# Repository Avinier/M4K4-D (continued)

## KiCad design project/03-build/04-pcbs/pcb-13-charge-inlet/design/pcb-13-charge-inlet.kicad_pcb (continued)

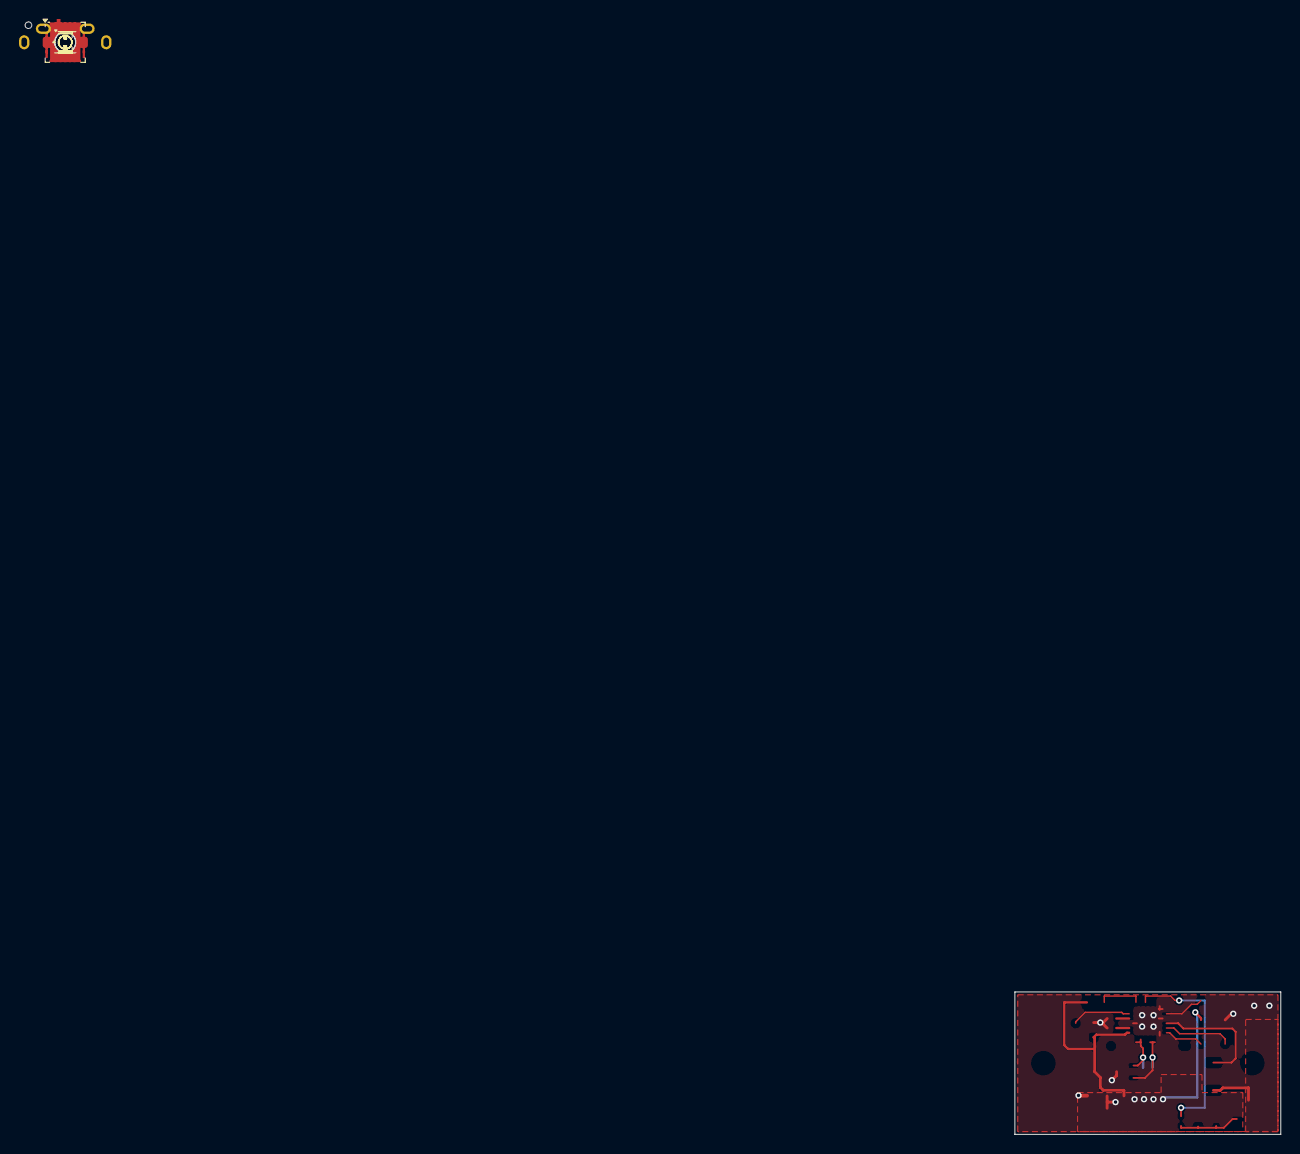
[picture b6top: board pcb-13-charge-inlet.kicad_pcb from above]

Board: 2 copper layers, 28.0 x 15.0 mm, 23 parts (1 on the bottom side), 15 nets.

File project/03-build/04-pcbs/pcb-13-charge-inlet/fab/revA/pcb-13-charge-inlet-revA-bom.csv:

"Comment","Designator","Footprint","Quantity","MPN","Manufacturer","Source","LCSC Part #"
"4.7u 50V","C1","Capacitor_SMD:C_1206_3216Metric","1","CL31B475KBHNNNE","Samsung","fab stock",""
"1u 50V","C2","Capacitor_SMD:C_0603_1608Metric","1","CL10B105KB8NNNC","Samsung","fab stock",""
"1u 10V","C3,C4","Capacitor_SMD:C_0402_1005Metric","2","CL05A105KP5NNNC","Samsung","fab stock",""
"100n 50V","C5","Capacitor_SMD:C_0603_1608Metric","1","CL10B104KB8NNNC","Samsung","fab stock",""
"TVS2200DRV","D1","Package_SON:WSON-6-1EP_2x2mm_P0.65mm_EP1x1.6mm","1","TVS2200DRVR","Texas Instruments","Mouser India 595-TVS2200DRVR (consigned)",""
"ESDA25W","D2","Package_TO_SOT_SMD:SOT-323_SC-70","1","ESDA25W","STMicroelectronics","element14 India 2341655 (consigned)",""
"STL6P3LLH6","Q1","pcb13:ST_PowerFLAT-3.3x3.3_TypeF","1","STL6P3LLH6","STMicroelectronics","element14 India 3132757 (consigned)",""
"1k","R1","Resistor_SMD:R_0805_2012Metric","1","ERJ-P06J102V","Panasonic","fab stock",""
"470","R2","Resistor_SMD:R_1206_3216Metric","1","ERJ-P08J471V","Panasonic","fab stock",""
"100k","R3","Resistor_SMD:R_0402_1005Metric","1","","","fab stock",""
"33k","R4","Resistor_SMD:R_0402_1005Metric","1","","","fab stock",""
"STUSB4500QTR","U1","Package_DFN_QFN:QFN-24-1EP_4x4mm_P0.5mm_EP2.7x2.7mm","1","STUSB4500QTR","STMicroelectronics","element14 India 2980889 (consigned)",""

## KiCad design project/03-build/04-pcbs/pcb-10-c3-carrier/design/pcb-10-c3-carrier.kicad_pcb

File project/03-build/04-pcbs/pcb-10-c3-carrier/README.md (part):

# PCB-10 — C3 controller carrier

Carrier for the C3 DevKitC: watchdog, READY, sleep gate, Hall and TCRT circuits.

| | |
|---|---|
| Register | [04-pcbs board register](../README.md#board-register) |
| Project BOM | CH-044 in [BOM.csv](../../BOM.csv) |
| Location | Body, −Y side wall |
| Specification | [RP-06 connector-schedule.md](../../../02-prototypes/RP-06-cad/connector-schedule.md)<br>[power-boards.md §2.4](../power-boards.md#24-logic-to-c3-j10-5--j10-6-gh-6)<br>[D-068](../../decisions.md#d-068) (mounting, DevKitC, watchdog, transceiver) |
| CAD placeholder | `c3_carrier()` in [`body_v1_model.py`](../../02-body/v1/cad/body_v1_model.py) |
| CAD labels | `C3_CARRIER_PCB10_WITH_DEVKITC` |
| Final CAD | `Custom PCBs › PCB-10 C3 controller carrier` in [makad-v1.step.py](../../final/v1/cad/makad-v1.step.py) |

## Stages

See [workflow.md](../workflow.md) for what each stage involves and when it is done.

| Stage | Status | Revision / evidence | Date |
|---|---|---|---|
| 1. Design | **Done: rev A** (lesson 5). DRC 0 errors, 0 unconnected, parity clean; fit in the robot 7/7; fab outputs in [`fab/revA/`](fab/revA/README.md); inputs frozen with [D-068](../../decisions.md#d-068) | [`check_pcb10_mount.py`](../../final/v1/cad/check_pcb10_mount.py) 9/9, [`check_pcb10_fit.py`](../../final/v1/cad/check_pcb10_fit.py) 7/7 | 2026-10-28 |
| 2. Procure | — | — | — |
| 3. Integrate | CAD replacement complete; physical integration/acceptance open | [Final CAD and verification](../../final/v1/README.md#pcb-geometry-in-the-whole-robot-assembly) | 2026-11-01 |

## Inputs

Frozen 2026-10-27 with [D-068](../../decisions.md#d-068): the builder left gaps 1–4 to the recommended options, asked for the genuine Espressif board only, and for the watchdog from the next best source.

**Spec sources.**

- RP-06 [connector-schedule.md](../../../02-prototypes/RP-06-cad/connector-schedule.md) `CN-06` and §3.3 (read-only): board, mounting, header rows.
- RP-02 [board-specs.md §7](../../../02-prototypes/RP-02-electrical/board-specs.md#7-safety-carrier-watchdog-block-c2-and-c3-carriers--decided-2026-09-25-bd-10) (`BD-10`, watchdog and READY) and §8 (inter-board signals); [compute-control-architecture.md](../../../02-prototypes/RP-02-electrical/compute-control-architecture.md) `CA-03`, `CA-05`, `CA-06`, `CA-10` and §3 (C3 I/O budget).
- RP-03 [base-control-architecture.md §3](../../../02-prototypes/RP-03-locomotion/base-control-architecture.md#3-pin-map-v01--esp32-s3-devkitc-1-n8) (pin map v0.1).
- [power-boards.md §2.4](../power-boards.md#24-logic-to-c3-j10-5--j10-6-gh-6) (`J10-5`/`J10-6`, AND gate, `FLT`) and §6 (D-041: no E-stop, `J10-11` not fitted).
- [D-013](../../decisions.md#d-013) and [nose-hall-board.md](../../01-chassis/v1/research/nose-hall-board.md) (`J10-8`); [D-016](../../decisions.md#d-016)/[D-021](../../decisions.md#d-021) and [rear-tcrt-lead.md](../../01-chassis/v1/research/rear-tcrt-lead.md) (`J10-10` and its circuit); [D-039](../../decisions.md#d-039) and [05-harness §5](../../05-harness/README.md#5-pinouts) (pinouts; encoders on the carrier 3V3); [D-048](../../decisions.md#d-048) (row repack).
- BOM rows CH-044 (this board) and CH-045 (DevKitC-1-N8).
- CAD: `C3_*` constants and `c3_carrier()` in [`body_v1_model.py`](../../02-body/v1/cad/body_v1_model.py), measured in the built body (*Envelope*).

**Datasheets read.** Espressif [ESP32-S3-DevKitC-1 v1.1 user guide](https://docs.espressif.com/projects/esp-dev-kits/en/latest/esp32s3/esp32-s3-devkitc-1/user_guide_v1.1.html), [dimension drawing](https://dl.espressif.com/dl/schematics/esp_idf/DXF_ESP32-S3-DevKitC-1_V1.1_20220429.pdf) and [schematic](https://dl.espressif.com/dl/schematics/SCH_ESP32-S3-DevKitC-1_V1.1_20221130.pdf); TI [THVD1451](https://www.ti.com/lit/ds/symlink/thvd1451.pdf) (SLLSEY3E), [TPS3436-Q1](https://www.ti.com/lit/ds/symlink/tps3436-q1.pdf) (SLVSGF1A), [SN74LVC1G08](https://www.ti.com/lit/ds/symlink/sn74lvc1g08.pdf), [SN74LVC1G11](https://www.ti.com/lit/ds/symlink/sn74lvc1g11.pdf), [DRV5055](https://www.ti.com/lit/ds/symlink/drv5055.pdf); Sharp [GP2Y0A21YK0F](https://global.sharp/products/device/lineup/data/pdf/datasheet/gp2y0a21yk_e.pdf); AOS AO3400A (LCSC C20917 page); ThinkRobotics [MOT3001 page](https://thinkrobotics.com/products/25mm-encoder-dc-metal-gearmotors).

### The DevKitC as built

The CAD's DevKitC (`ESP32-S3-WROOM-1_devkit_2xUSBC_c.step`, a FreeCAD model of a generic board) is **not** Espressif's DevKitC-1 v1.1:

| | CAD STEP | Espressif v1.1 (drawing) |
|---|---|---|
| Board width | 28.3 mm | **25.40 mm** |
| Header row spacing | 25.4 mm | **22.86 mm** (pins 1.27 mm in from each long edge) |
| Pins | 2 × 22, 2.54 mm pitch | Same |
| Antenna end past pin 1 | 8.2 mm | about 7.9 mm (module overhangs the board end by about 6.4 mm) |
| USB end past pin 22 | 2.6 mm | **8.0 mm** (two USB-C) |
| Pins modelled | No, only the 44 pad holes | — |
| Bottom side | Flat | Flat; header plastic 2.5 mm; USB shell legs and solder joints not dimensioned (`U`) |

The carrier footprint uses the v1.1 drawing. Keeping the CAD's pin columns and row centre: pins at X −8.49 + 2.54 k (k 0…21), **J1 row at Z 98.92, J3 row at Z 121.78**, board Z 97.65–123.05. Pin 1 of both rows is at the antenna end, X 44.85; the USB ports face −X with their fronts at about **X −16.5**, 2.5 mm past the carrier's −X edge and inside the service corridor. Seen from the component side with the antenna up, J1 is on the left, the `UART` port bottom-left and the `USB` port bottom-right. In the robot that puts J1 low, J3 high, the UART port at about Z 103 and the native USB port at about Z 117.

Header pins (user guide, v1.1):

| Pin | 1 | 2 | 3 | 4 | 5 | 6 | 7 | 8 | 9 | 10 | 11 | 12 | 13 | 14 | 15 | 16 | 17 | 18 | 19 | 20 | 21 | 22 |
|---|---|---|---|---|---|---|---|---|---|---|---|---|---|---|---|---|---|---|---|---|---|---|
| J1 | 3V3 | 3V3 | RST (EN) | 4 | 5 | 6 | 7 | 15 | 16 | 17 | 18 | 8 | 3 | 46 | 9 | 10 | 11 | 12 | 13 | 14 | 5V | G |
| J3 | G | 43 TX | 44 RX | 1 | 2 | 42 | 41 | 40 | 39 | 38 | 37 | 36 | 35 | 0 | 45 | 48 | 47 | 21 | 20 | 19 | G | G |

Two facts the pin map v0.1 did not have:

- **On v1.1 the RGB LED is on GPIO38**, not GPIO48 (v1.0 had it on 48). So GPIO48 is free for `WDI` on v1.1, and GPIO38 drives the LED's data input, so it is not a clean spare. On a v1.0 board `WDI` would also clock the LED: harmless flicker, no fault.
- **The 5V header pin is `VCC_5V`, downstream of the USB diodes** (1N5819 from each USB `VBUS`). A service USB cable therefore powers the carrier's 5 V net, and through `J10-1` it back-feeds `W11` into PCB-04's `PB-SAFE-BASE` output and the GP2Y. See gap 4.

GPIO35–37 are free on the N8 module (they go to octal PSRAM only on R8 variants, `CA-03`).

### GPIO map (v0.3, set at layout)

v0.2 (D-068) assigned the pins by function; v0.3 reassigns them at placement (lesson 4, 2026-10-28) so that every track runs from its DevKitC pin to its connector without crossing another. The bottom pin row (J1, nearest the connectors) feeds the connectors in their left-to-right order; the top row (J3) carries the signals that go further down (row B and C connectors) and the watchdog cluster. The roles are unchanged and every rule still holds: no strapping or USB pins, the three analog inputs on ADC1, `MCU_RDY`/`WDI`/`NSLEEP` on plain GPIO, LEDC, PCNT, UART1 and the IMU's SPI through the GPIO matrix (the IMU runs at 10 MHz or less).

| Function | GPIO | DevKitC pin | Carrier net / connector | v0.2 |
|---|---:|---|---|---:|
| `TCRT_LED_EN` | 4 | J1-4 | Q1 gate (100 kΩ pull-down) | 47 |
| `TCRT_ADC` (ADC1_CH4) | 5 | J1-5 | R37 1 kΩ from `TCRT_OUT`, `J10-10` pin 3 | 8 |
| `ENC_R_A`, `ENC_R_B` | 6, 7 | J1-6, J1-7 | `J10-4` pins 3, 4 | 6, 7 |
| `ENC_L_A`, `ENC_L_B` | 15, 16 | J1-8, J1-9 | `J10-3` pins 3, 4 | 4, 5 |
| `MOTOR_PRESENT` | 17 | J1-10 | `J10-12` pin 3 (1 kΩ, 100 kΩ pull-down) | 40 |
| `nFAULT` | 18 | J1-11 | `FLT` (`J10-5`/`J10-6` pin 4) through 1 kΩ, 10 kΩ pull-up | 9 |
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
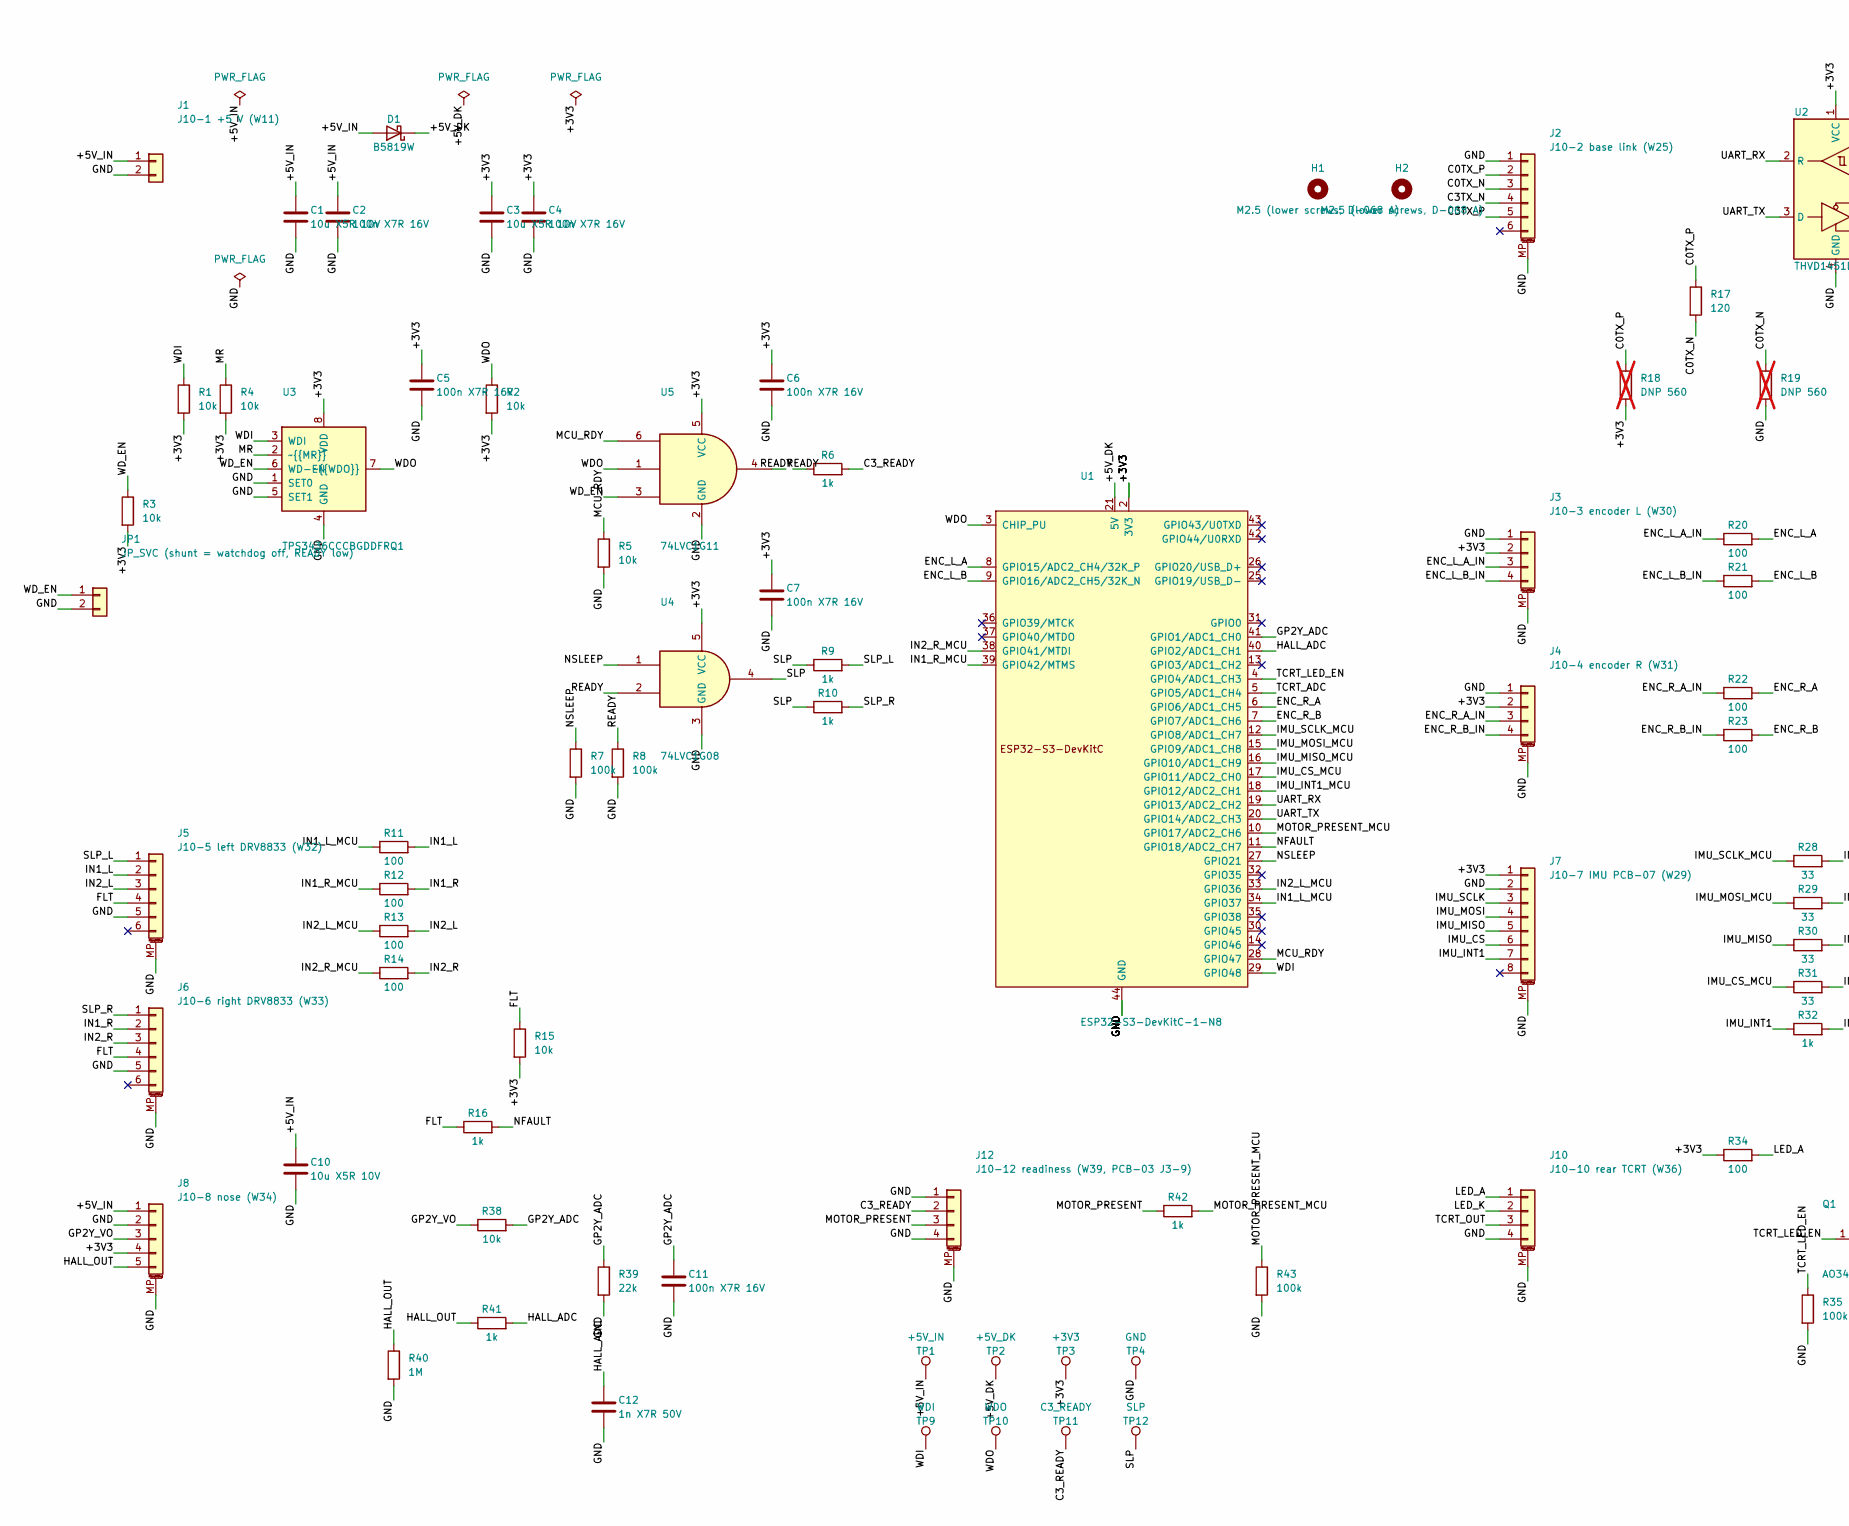
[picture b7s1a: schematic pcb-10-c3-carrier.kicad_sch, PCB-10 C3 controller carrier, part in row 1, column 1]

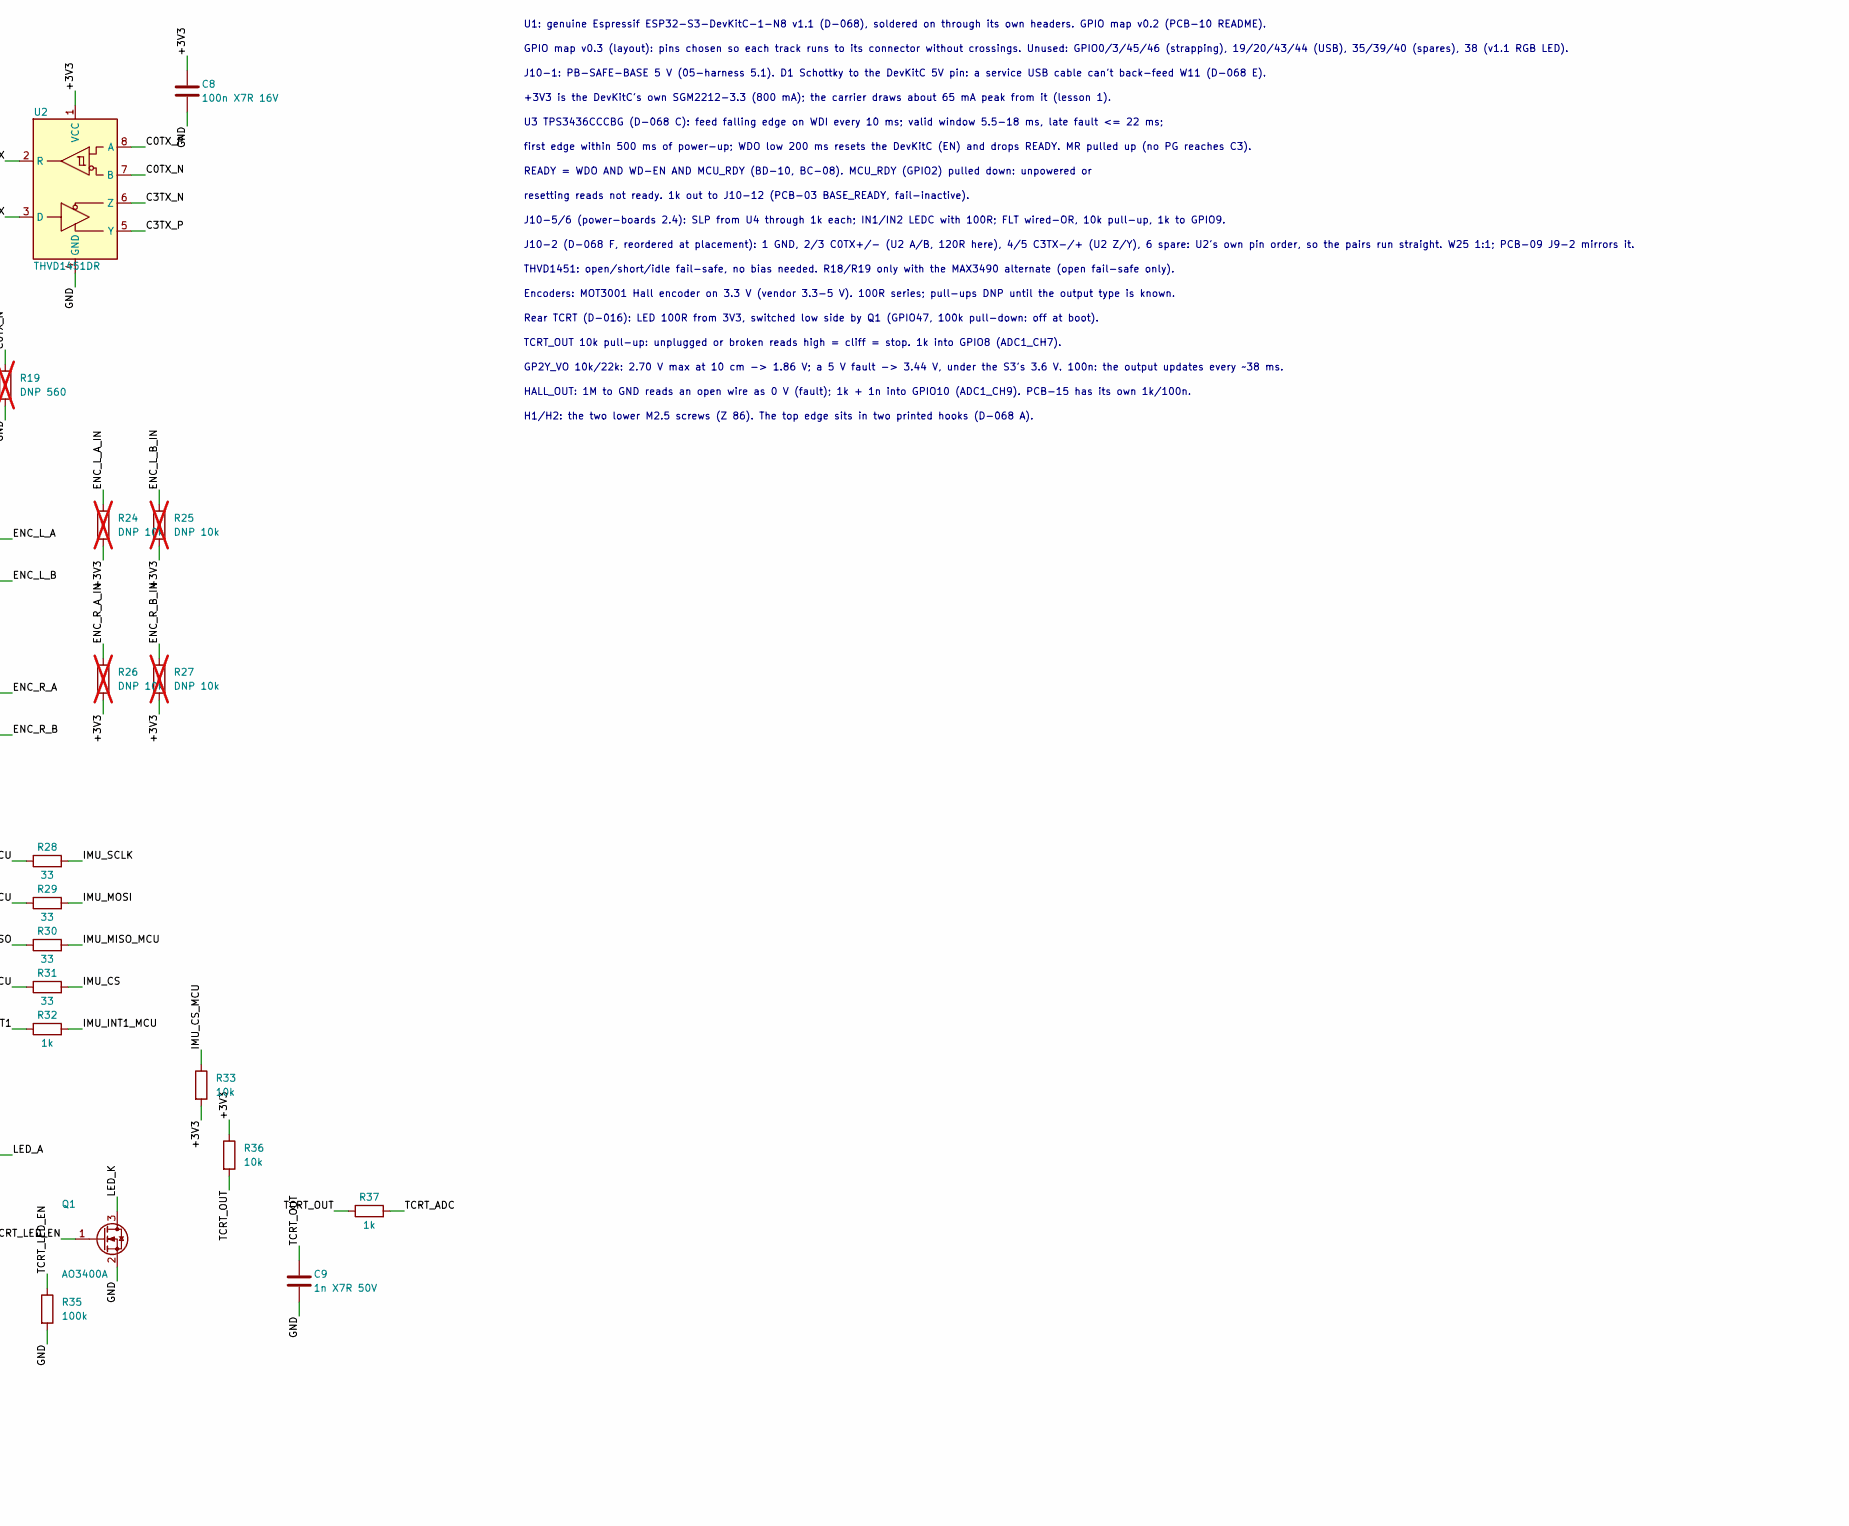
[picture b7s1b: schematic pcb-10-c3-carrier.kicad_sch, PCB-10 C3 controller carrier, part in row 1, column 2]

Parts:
C1, C3, C10: 10u X5R 10V; C_0805_2012Metric
C2, C4, C5, C6, C7, C8, C11: 100n X7R 16V; C_0402_1005Metric
C9, C12: 1n X7R 50V; C_0402_1005Metric
D1: B5819W; D_SOD-123; MPN B5819W; LCSC C8598
H1, H2: M2.5 (lower screws, D-068 A); MountingHole_2.7mm_M2.5
J1: J10-1 +5 V (W11); Molex_Micro-Fit_3.0_43650-0200_1x02_P3.00mm_Horizontal; MPN 43650-0200
J2: J10-2 base link (W25); JST_GH_BM06B-GHS-TBT_1x06-1MP_P1.25mm_Vertical; MPN BM06B-GHS-TBT
J3: J10-3 encoder L (W30); JST_GH_BM04B-GHS-TBT_1x04-1MP_P1.25mm_Vertical; MPN BM04B-GHS-TBT
J4: J10-4 encoder R (W31); JST_GH_BM04B-GHS-TBT_1x04-1MP_P1.25mm_Vertical; MPN BM04B-GHS-TBT
J5: J10-5 left DRV8833 (W32); JST_GH_BM06B-GHS-TBT_1x06-1MP_P1.25mm_Vertical; MPN BM06B-GHS-TBT
J6: J10-6 right DRV8833 (W33); JST_GH_BM06B-GHS-TBT_1x06-1MP_P1.25mm_Vertical; MPN BM06B-GHS-TBT
J7: J10-7 IMU PCB-07 (W29); JST_GH_BM08B-GHS-TBT_1x08-1MP_P1.25mm_Vertical; MPN BM08B-GHS-TBT
J8: J10-8 nose (W34); JST_GH_BM05B-GHS-TBT_1x05-1MP_P1.25mm_Vertical; MPN BM05B-GHS-TBT
J10: J10-10 rear TCRT (W36); JST_GH_BM04B-GHS-TBT_1x04-1MP_P1.25mm_Vertical; MPN BM04B-GHS-TBT
J12: J10-12 readiness (W39, PCB-03 J3-9); JST_GH_BM04B-GHS-TBT_1x04-1MP_P1.25mm_Vertical; MPN BM04B-GHS-TBT
JP1: JP_SVC (shunt = watchdog off, READY low); PinHeader_1x02_P2.00mm_Vertical
Q1: AO3400A; SOT-23; MPN AO3400A; LCSC C20917
R1, R2, R3, R4, R5, R15, R33, R38: 10k; R_0402_1005Metric
R6, R9, R10, R16, R32, R37, R41, R42: 1k; R_0402_1005Metric
R7, R8, R35, R43: 100k; R_0402_1005Metric
R11, R12, R13, R14, R20, R21, R22, R23: 100; R_0402_1005Metric
R17: 120; R_0402_1005Metric
R18, R19: DNP 560; R_0402_1005Metric; not fitted
R24, R25, R26, R27: DNP 10k; R_0402_1005Metric; not fitted
R28, R29, R30, R31: 33; R_0402_1005Metric
R34: 100; R_0603_1608Metric
R36: 10k; R_0603_1608Metric
R39: 22k; R_0402_1005Metric
R40: 1M; R_0402_1005Metric
TP1: +5V_IN; TestPoint_Pad_D1.0mm
TP2: +5V_DK; TestPoint_Pad_D1.0mm
TP3: +3V3; TestPoint_Pad_D1.0mm
TP4: GND; TestPoint_Pad_D1.0mm
TP9: WDI; TestPoint_Pad_D1.0mm
TP10: WDO; TestPoint_Pad_D1.0mm
TP11: C3_READY; TestPoint_Pad_D1.0mm
TP12: SLP; TestPoint_Pad_D1.0mm
U1: ESP32-S3-DevKitC-1-N8; ESP32-S3-DevKitC-1_v1.1_1.0mm; MPN ESP32-S3-DevKitC-1-N8 (board v1.1)
U2: THVD1451DR; SOIC-8_3.9x4.9mm_P1.27mm; MPN THVD1451DR
U3: TPS3436CCCBGDDFRQ1; Texas_DDF0008A_SOT-8_1.6x2.9mm_P0.65mm; MPN TPS3436CCCBGDDFRQ1
U4: 74LVC1G08; SOT-23-5; MPN SN74LVC1G08DBVR; LCSC C7666
U5: 74LVC1G11; SOT-23-6; MPN SN74LVC1G11DBVR; LCSC C22046

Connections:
/+3V3: C3.1, C4.1, C5.1, C6.1, C7.1, C8.1, J3.2, J4.2, J7.1, J8.4, R1.2, R2.2, R3.2, R4.2, R15.2, R18.2, R24.2, R25.2, R26.2, R27.2, R33.2, R34.1, R36.1, TP3.1 (1_1), U1.1 (3V3), U1.2 (3V3), U2.1 (VCC), U3.8 (VDD), U4.5 (VCC), U5.5 (VCC)
/+5V_DK: D1.1 (K), TP2.1 (1_1), U1.21 (5V)
/+5V_IN: C1.1, C2.1, C10.1, D1.2 (A), J1.1, J8.1, TP1.1 (1_1)
/C0TX_N: J2.3, R17.2, R19.1, U2.7 (B)
/C0TX_P: J2.2, R17.1, R18.1, U2.8 (A)
/C3TX_N: J2.4, U2.6 (Z)
/C3TX_P: J2.5, U2.5 (Y)
/C3_READY: J12.2, R6.2, TP11.1 (1_1)
/ENC_L_A: R20.2, U1.8 (GPIO15/ADC2_CH4/32K_P)
/ENC_L_A_IN: J3.3, R20.1, R24.1
/ENC_L_B: R21.2, U1.9 (GPIO16/ADC2_CH5/32K_N)
/ENC_L_B_IN: J3.4, R21.1, R25.1
/ENC_R_A: R22.2, U1.6 (GPIO6/ADC1_CH5)
/ENC_R_A_IN: J4.3, R22.1, R26.1
/ENC_R_B: R23.2, U1.7 (GPIO7/ADC1_CH6)
/ENC_R_B_IN: J4.4, R23.1, R27.1
/FLT: J5.4, J6.4, R15.1, R16.1
/GND: C1.2, C2.2, C3.2, C4.2, C5.2, C6.2, C7.2, C8.2, C9.2, C10.2, C11.2, C12.2, J1.2, J2.1, J2.MP (MountPin), J3.1, J3.MP (MountPin), J4.1, J4.MP (MountPin), J5.5, J5.MP (MountPin), J6.5, J6.MP (MountPin), J7.2, J7.MP (MountPin), J8.2, J8.MP (MountPin), J10.4, J10.MP (MountPin), J12.1, J12.4, J12.MP (MountPin), JP1.2, Q1.2 (S), R5.2, R7.2, R8.2, R19.2, R35.2, R39.2, R40.2, R43.2, TP4.1 (1_1), U1.22 (GND), U1.23 (GND), U1.24 (GND), U1.44 (GND), U2.4 (GND), U3.1 (SET0), U3.4 (GND), U3.5 (SET1), U4.3 (GND), U5.2 (GND)
/GP2Y_ADC: C11.1, R38.2, R39.1, U1.41 (GPIO1/ADC1_CH0)
/GP2Y_VO: J8.3, R38.1
/HALL_ADC: C12.1, R41.2, U1.40 (GPIO2/ADC1_CH1)
/HALL_OUT: J8.5, R40.1, R41.1
/IMU_CS: J7.6, R31.2
/IMU_CS_MCU: R31.1, R33.1, U1.17 (GPIO11/ADC2_CH0)
/IMU_INT1: J7.7, R32.1
/IMU_INT1_MCU: R32.2, U1.18 (GPIO12/ADC2_CH1)
/IMU_MISO: J7.5, R30.1
/IMU_MISO_MCU: R30.2, U1.16 (GPIO10/ADC1_CH9)
/IMU_MOSI: J7.4, R29.2
/IMU_MOSI_MCU: R29.1, U1.15 (GPIO9/ADC1_CH8)
/IMU_SCLK: J7.3, R28.2
/IMU_SCLK_MCU: R28.1, U1.12 (GPIO8/ADC1_CH7)
/IN1_L: J5.2, R11.2
/IN1_L_MCU: R11.1, U1.34 (GPIO37)
/IN1_R: J6.2, R12.2
/IN1_R_MCU: R12.1, U1.39 (GPIO42/MTMS)
/IN2_L: J5.3, R13.2
/IN2_L_MCU: R13.1, U1.33 (GPIO36)
/IN2_R: J6.3, R14.2
/IN2_R_MCU: R14.1, U1.38 (GPIO41/MTDI)
/LED_A: J10.1, R34.2
/LED_K: J10.2, Q1.3 (D)
/MCU_RDY: R5.1, U1.28 (GPIO47), U5.6
/MOTOR_PRESENT: J12.3, R42.1
/MOTOR_PRESENT_MCU: R42.2, R43.1, U1.10 (GPIO17/ADC2_CH6)
/MR: R4.1, U3.2 (~{MR})
/NFAULT: R16.2, U1.11 (GPIO18/ADC2_CH7)
/NSLEEP: R7.1, U1.27 (GPIO21), U4.1
/READY: R6.1, R8.1, U4.2, U5.4
/SLP: R9.1, R10.1, TP12.1 (1_1), U4.4
/SLP_L: J5.1, R9.2
/SLP_R: J6.1, R10.2
/TCRT_ADC: R37.2, U1.5 (GPIO5/ADC1_CH4)
/TCRT_LED_EN: Q1.1 (G), R35.1, U1.4 (GPIO4/ADC1_CH3)
/TCRT_OUT: C9.1, J10.3, R36.2, R37.1
/UART_RX: U1.19 (GPIO13/ADC2_CH2), U2.2 (R)
/UART_TX: U1.20 (GPIO14/ADC2_CH3), U2.3 (D)
/WDI: R1.1, TP9.1 (1_1), U1.29 (GPIO48), U3.3 (WDI)
/WDO: R2.1, TP10.1 (1_1), U1.3 (CHIP_PU), U3.7 (~{WDO}), U5.1
/WD_EN: JP1.1, R3.1, U3.6 (WD-EN), U5.3

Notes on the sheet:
U1: genuine Espressif ESP32-S3-DevKitC-1-N8 v1.1 (D-068), soldered on through its own headers. GPIO map v0.2 (PCB-10 README).
GPIO map v0.3 (layout): pins chosen so each track runs to its connector without crossings. Unused: GPIO0/3/45/46 (strapping), 19/20/43/44 (USB), 35/39/40 (spares), 38 (v1.1 RGB LED).
J10-1: PB-SAFE-BASE 5 V (05-harness 5.1). D1 Schottky to the DevKitC 5V pin: a service USB cable can't back-feed W11 (D-068 E).
+3V3 is the DevKitC's own SGM2212-3.3 (800 mA); the carrier draws about 65 mA peak from it (lesson 1).
U3 TPS3436CCCBG (D-068 C): feed falling edge on WDI every 10 ms; valid window 5.5-18 ms, late fault <= 22 ms;
first edge within 500 ms of power-up; WDO low 200 ms resets the DevKitC (EN) and drops READY. MR pulled up (no PG reaches C3).
READY = WDO AND WD-EN AND MCU_RDY (BD-10, BC-08). MCU_RDY (GPIO2) pulled down: unpowered or
resetting reads not ready. 1k out to J10-12 (PCB-03 BASE_READY, fail-inactive).
J10-5/6 (power-boards 2.4): SLP from U4 through 1k each; IN1/IN2 LEDC with 100R; FLT wired-OR, 10k pull-up, 1k to GPIO9.
J10-2 (D-068 F, reordered at placement): 1 GND, 2/3 C0TX+/- (U2 A/B, 120R here), 4/5 C3TX-/+ (U2 Z/Y), 6 spare: U2's own pin order, so the pairs run straight. W25 1:1; PCB-09 J9-2 mirrors it.
THVD1451: open/short/idle fail-safe, no bias needed. R18/R19 only with the MAX3490 alternate (open fail-safe only).
Encoders: MOT3001 Hall encoder on 3.3 V (vendor 3.3-5 V). 100R series; pull-ups DNP until the output type is known.
Rear TCRT (D-016): LED 100R from 3V3, switched low side by Q1 (GPIO47, 100k pull-down: off at boot).
TCRT_OUT 10k pull-up: unplugged or broken reads high = cliff = stop. 1k into GPIO8 (ADC1_CH7).
GP2Y_VO 10k/22k: 2.70 V max at 10 cm -> 1.86 V; a 5 V fault -> 3.44 V, under the S3's 3.6 V. 100n: the output updates every ~38 ms.
HALL_OUT: 1M to GND reads an open wire as 0 V (fault); 1k + 1n into GPIO10 (ADC1_CH9). PCB-15 has its own 1k/100n.
H1/H2: the two lower M2.5 screws (Z 86). The top edge sits in two printed hooks (D-068 A).

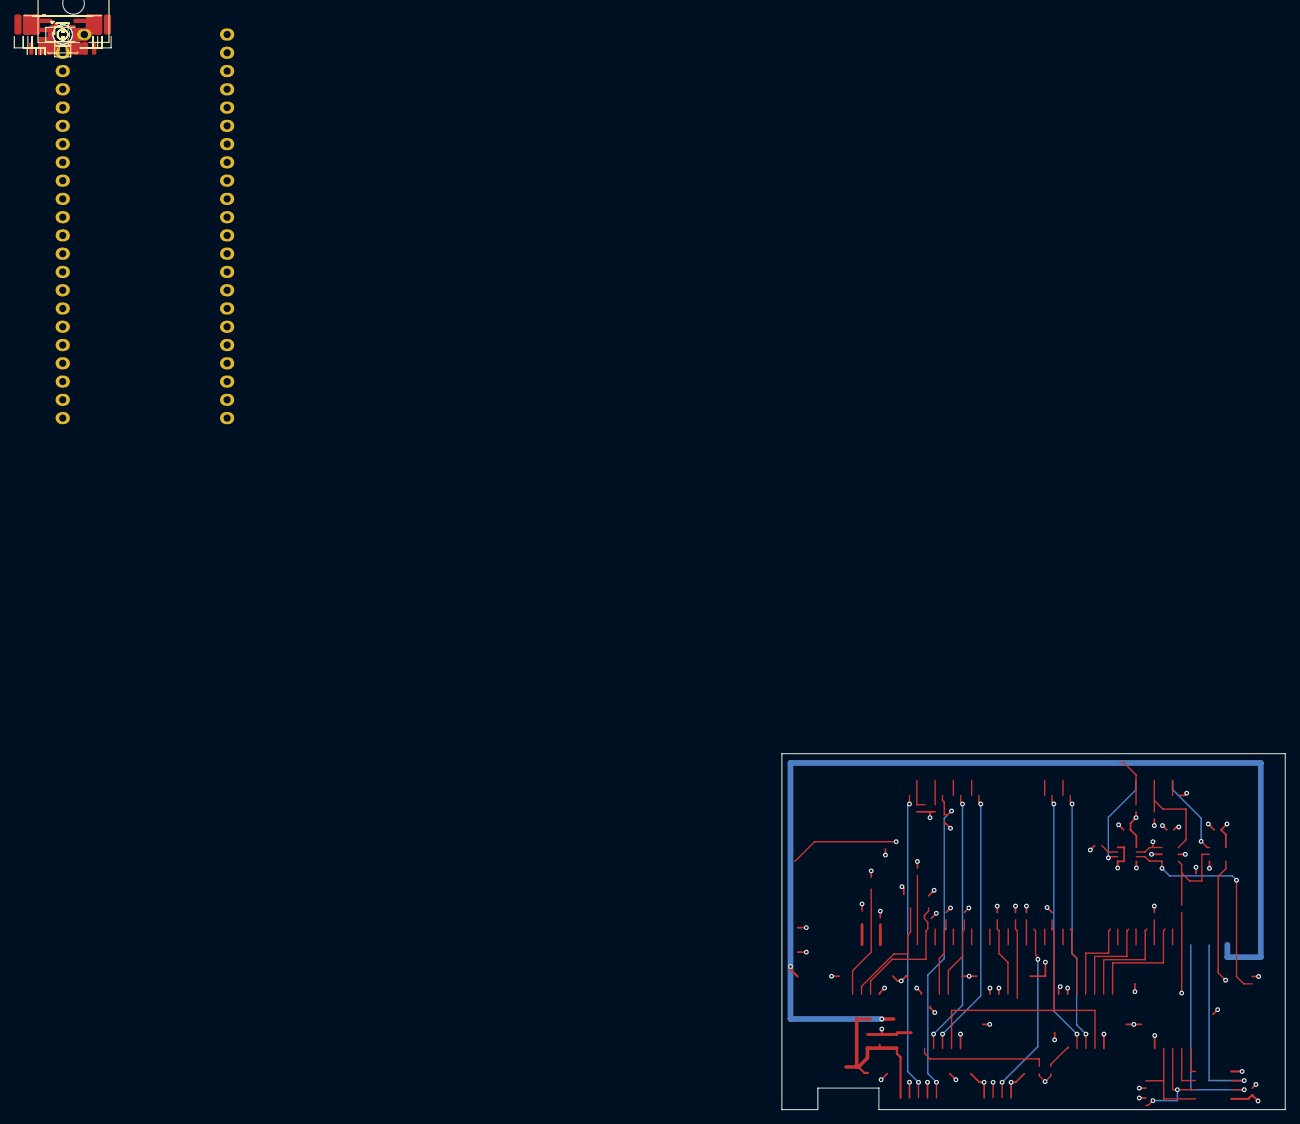
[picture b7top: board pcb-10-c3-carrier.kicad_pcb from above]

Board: 4 copper layers, 70.0 x 49.5 mm, 83 parts (0 on the bottom side), 60 nets.

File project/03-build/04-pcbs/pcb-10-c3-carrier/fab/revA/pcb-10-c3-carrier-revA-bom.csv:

"Comment","Designator","Footprint","Quantity","MPN","Manufacturer","LCSC Part #"
"10u X5R 10V","C1,C3,C10","Capacitor_SMD:C_0805_2012Metric","3","","",""
"100n X7R 16V","C2,C4,C5,C6,C7,C8,C11","Capacitor_SMD:C_0402_1005Metric","7","","",""
"1n X7R 50V","C9,C12","Capacitor_SMD:C_0402_1005Metric","2","","",""
"B5819W","D1","Diode_SMD:D_SOD-123","1","B5819W","","C8598"
"J10-1 +5 V (W11)","J1","pcb10:Molex_Micro-Fit_3.0_43650-0200_1x02_P3.00mm_Horizontal","1","43650-0200","Molex",""
"J10-2 base link (W25)","J2","Connector_JST:JST_GH_BM06B-GHS-TBT_1x06-1MP_P1.25mm_Vertical","1","BM06B-GHS-TBT","JST",""
"J10-3 encoder L (W30)","J3","Connector_JST:JST_GH_BM04B-GHS-TBT_1x04-1MP_P1.25mm_Vertical","1","BM04B-GHS-TBT","JST",""
"J10-4 encoder R (W31)","J4","Connector_JST:JST_GH_BM04B-GHS-TBT_1x04-1MP_P1.25mm_Vertical","1","BM04B-GHS-TBT","JST",""
"J10-5 left DRV8833 (W32)","J5","Connector_JST:JST_GH_BM06B-GHS-TBT_1x06-1MP_P1.25mm_Vertical","1","BM06B-GHS-TBT","JST",""
"J10-6 right DRV8833 (W33)","J6","Connector_JST:JST_GH_BM06B-GHS-TBT_1x06-1MP_P1.25mm_Vertical","1","BM06B-GHS-TBT","JST",""
"J10-7 IMU PCB-07 (W29)","J7","Connector_JST:JST_GH_BM08B-GHS-TBT_1x08-1MP_P1.25mm_Vertical","1","BM08B-GHS-TBT","JST",""
"J10-8 nose (W34)","J8","Connector_JST:JST_GH_BM05B-GHS-TBT_1x05-1MP_P1.25mm_Vertical","1","BM05B-GHS-TBT","JST",""
"J10-10 rear TCRT (W36)","J10","Connector_JST:JST_GH_BM04B-GHS-TBT_1x04-1MP_P1.25mm_Vertical","1","BM04B-GHS-TBT","JST",""
"J10-12 readiness (W39, PCB-03 J3-9)","J12","Connector_JST:JST_GH_BM04B-GHS-TBT_1x04-1MP_P1.25mm_Vertical","1","BM04B-GHS-TBT","JST",""
"JP_SVC (shunt = watchdog off, READY low)","JP1","Connector_PinHeader_2.00mm:PinHeader_1x02_P2.00mm_Vertical","1","","",""
"AO3400A","Q1","Package_TO_SOT_SMD:SOT-23","1","AO3400A","AOS","C20917"
"10k","R1,R2,R3,R4,R5,R15,R33,R38","Resistor_SMD:R_0402_1005Metric","8","","",""
"1k","R6,R9,R10,R16,R32,R37,R41,R42","Resistor_SMD:R_0402_1005Metric","8","","",""
"100k","R7,R8,R35,R43","Resistor_SMD:R_0402_1005Metric","4","","",""
"100","R11,R12,R13,R14,R20,R21,R22,R23","Resistor_SMD:R_0402_1005Metric","8","","",""
"120","R17","Resistor_SMD:R_0402_1005Metric","1","","",""
"33","R28,R29,R30,R31","Resistor_SMD:R_0402_1005Metric","4","","",""
"100","R34","Resistor_SMD:R_0603_1608Metric","1","","",""
"10k","R36","Resistor_SMD:R_0603_1608Metric","1","","",""
"22k","R39","Resistor_SMD:R_0402_1005Metric","1","","",""
"1M","R40","Resistor_SMD:R_0402_1005Metric","1","","",""
"THVD1451DR","U2","Package_SO:SOIC-8_3.9x4.9mm_P1.27mm","1","THVD1451DR","Texas Instruments",""
"TPS3436CCCBGDDFRQ1","U3","pcb10:Texas_DDF0008A_SOT-8_1.6x2.9mm_P0.65mm","1","TPS3436CCCBGDDFRQ1","Texas Instruments",""
"74LVC1G08","U4","Package_TO_SOT_SMD:SOT-23-5","1","SN74LVC1G08DBVR","Texas Instruments","C7666"
"74LVC1G11","U5","Package_TO_SOT_SMD:SOT-23-6","1","SN74LVC1G11DBVR","Texas Instruments","C22046"

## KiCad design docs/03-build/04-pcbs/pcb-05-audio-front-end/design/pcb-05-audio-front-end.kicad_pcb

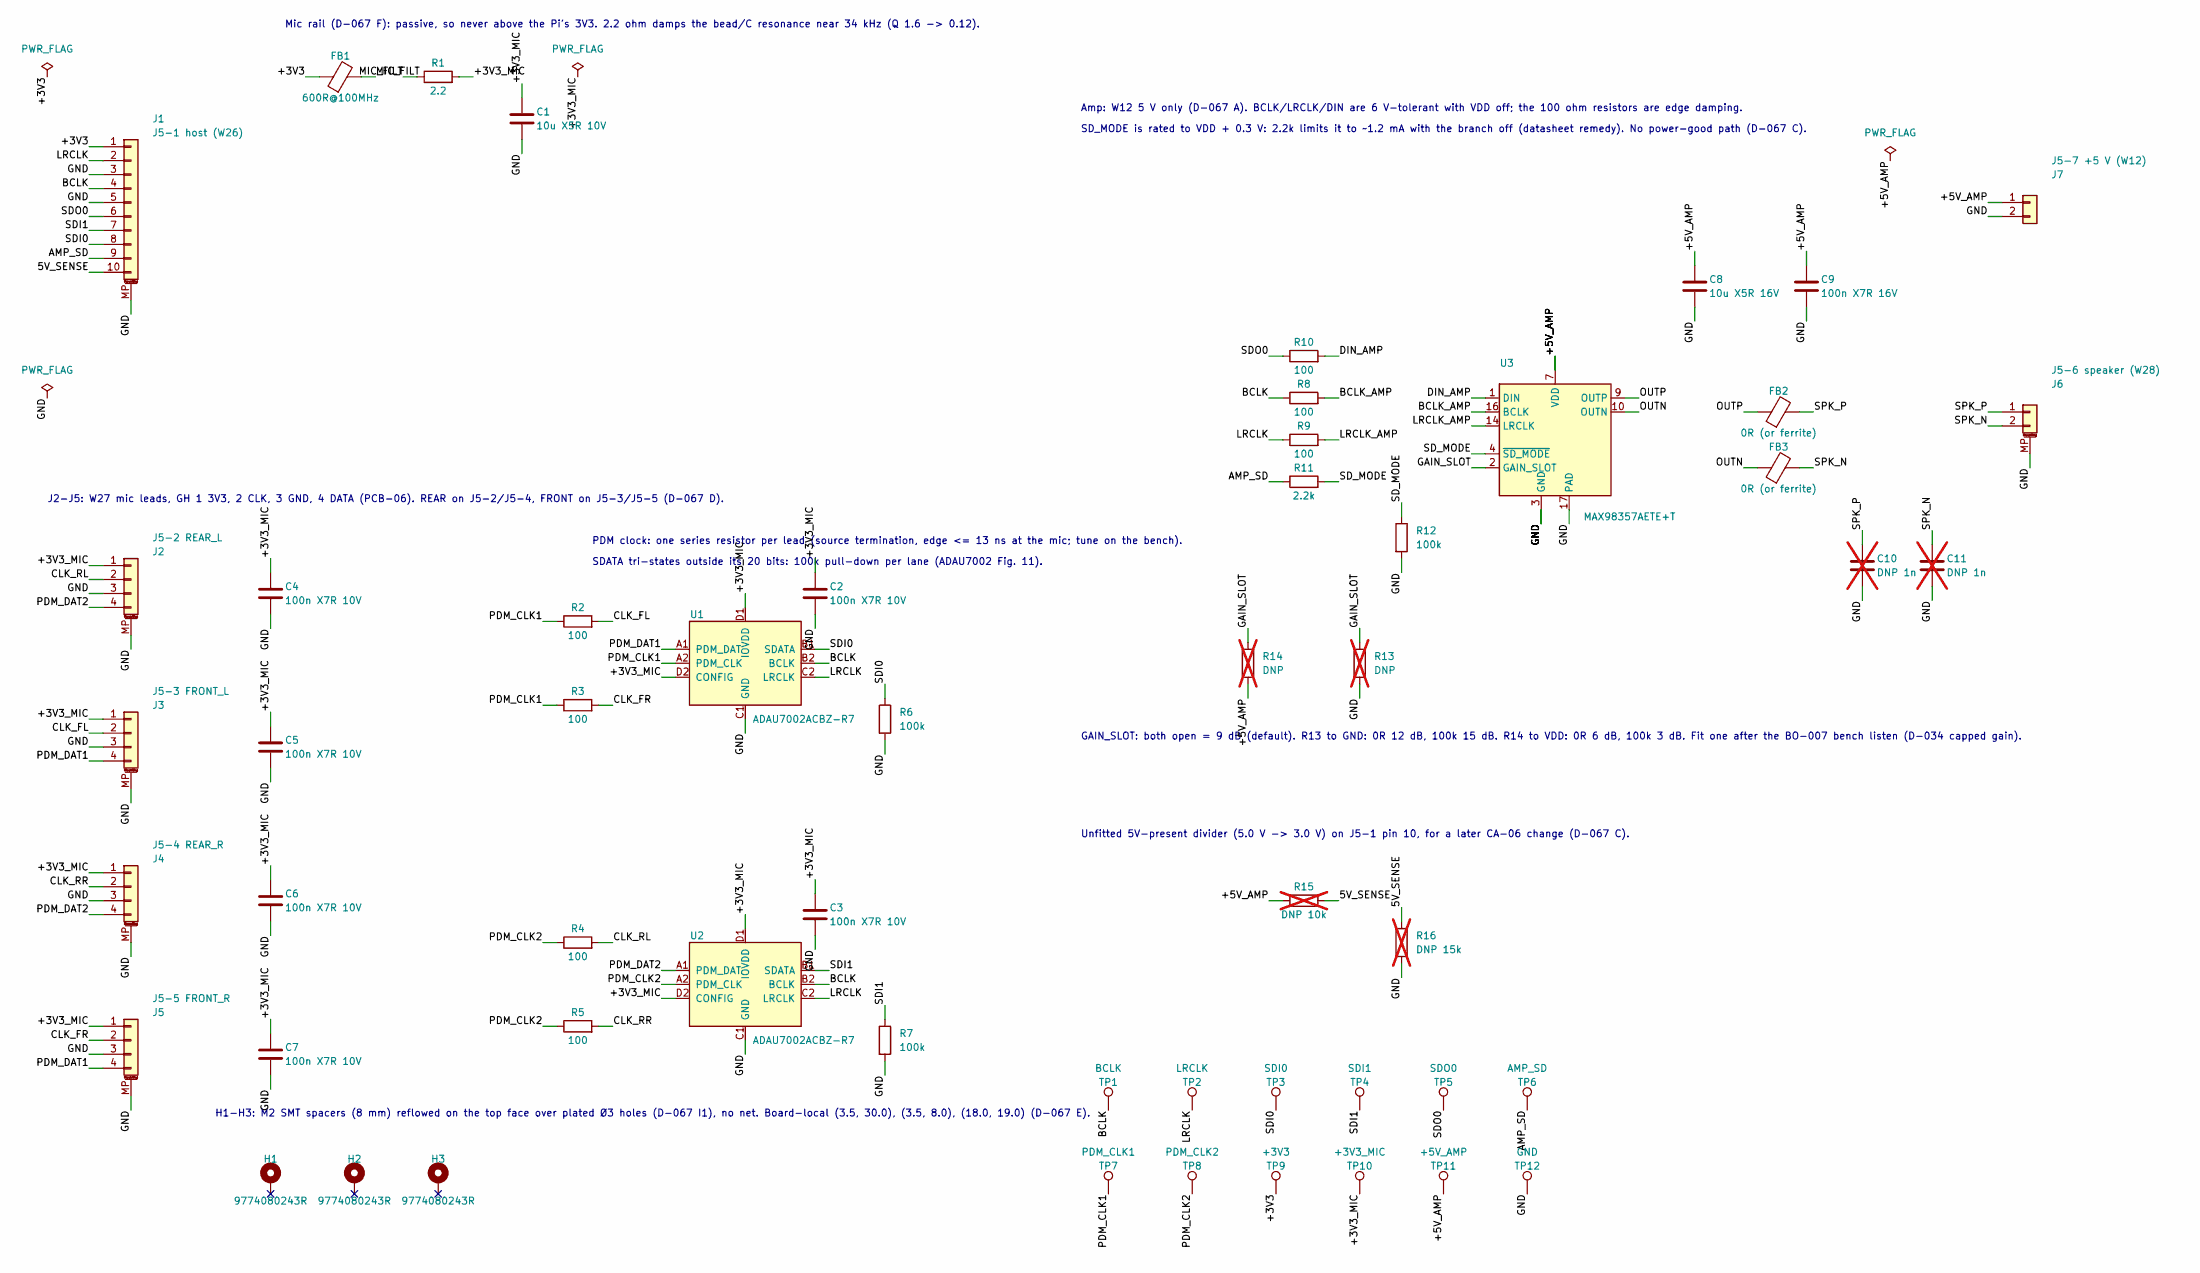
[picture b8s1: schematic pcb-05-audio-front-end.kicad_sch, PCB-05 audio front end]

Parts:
C1: 10u X5R 10V; C_0805_2012Metric
C2, C3, C4, C5, C6, C7: 100n X7R 10V; C_0402_1005Metric
C8: 10u X5R 16V; C_0805_2012Metric
C9: 100n X7R 16V; C_0402_1005Metric
C10, C11: DNP 1n; C_0402_1005Metric; not fitted
FB1: 600R@100MHz; L_0603_1608Metric
FB2, FB3: 0R (or ferrite); L_0603_1608Metric
H1, H2, H3: 9774080243R; Wurth_WA-SMSI-M2_H8mm_9774080243_PTH; MPN 9774080243R
J1: J5-1 host (W26); JST_GH_SM10B-GHS-TB_1x10-1MP_P1.25mm_Horizontal; MPN SM10B-GHS-TB(LF)(SN)
J2: J5-2 REAR_L; JST_GH_SM04B-GHS-TB_1x04-1MP_P1.25mm_Horizontal; MPN SM04B-GHS-TB(LF)(SN)
J3: J5-3 FRONT_L; JST_GH_SM04B-GHS-TB_1x04-1MP_P1.25mm_Horizontal; MPN SM04B-GHS-TB(LF)(SN)
J4: J5-4 REAR_R; JST_GH_SM04B-GHS-TB_1x04-1MP_P1.25mm_Horizontal; MPN SM04B-GHS-TB(LF)(SN)
J5: J5-5 FRONT_R; JST_GH_SM04B-GHS-TB_1x04-1MP_P1.25mm_Horizontal; MPN SM04B-GHS-TB(LF)(SN)
J6: J5-6 speaker (W28); JST_GH_SM02B-GHS-TB_1x02-1MP_P1.25mm_Horizontal; MPN SM02B-GHS-TB(LF)(SN)
J7: J5-7 +5 V (W12); Molex_Micro-Fit_3.0_43650-0200_1x02_P3.00mm_Horizontal; MPN 43650-0200
R1: 2.2; R_0402_1005Metric
R2, R3, R4, R5, R8, R9, R10: 100; R_0402_1005Metric
R6, R7, R12: 100k; R_0402_1005Metric
R11: 2.2k; R_0402_1005Metric
R13, R14: DNP; R_0402_1005Metric; not fitted
R15: DNP 10k; R_0402_1005Metric; not fitted
R16: DNP 15k; R_0402_1005Metric; not fitted
TP1: BCLK; TestPoint_Pad_D1.0mm
TP2: LRCLK; TestPoint_Pad_D1.0mm
TP3: SDI0; TestPoint_Pad_D1.0mm
TP4: SDI1; TestPoint_Pad_D1.0mm
TP5: SDO0; TestPoint_Pad_D1.0mm
TP6: AMP_SD; TestPoint_Pad_D1.0mm
TP7: PDM_CLK1; TestPoint_Pad_D1.0mm
TP8: PDM_CLK2; TestPoint_Pad_D1.0mm
TP9: +3V3; TestPoint_Pad_D1.0mm
TP10: +3V3_MIC; TestPoint_Pad_D1.0mm
TP11: +5V_AMP; TestPoint_Pad_D1.0mm
TP12: GND; TestPoint_Pad_D1.0mm
U1, U2: ADAU7002ACBZ-R7; ADAU7002_WLCSP-8_0.76x1.56mm_P0.4mm; MPN ADAU7002ACBZ-R7; LCSC C481886
U3: MAX98357AETE+T; TQFN-16-1EP_3x3mm_P0.5mm_EP1.23x1.23mm; MPN MAX98357AETE+T; LCSC C910544

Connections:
/5V_SENSE: J1.10, R15.2, R16.1
/+3V3: FB1.1, J1.1, TP9.1 (1_1)
/+3V3_MIC: C1.1, C2.1, C3.1, C4.1, C5.1, C6.1, C7.1, J2.1, J3.1, J4.1, J5.1, R1.2, TP10.1 (1_1), U1.D1 (IOVDD), U1.D2 (CONFIG), U2.D1 (IOVDD), U2.D2 (CONFIG)
/+5V_AMP: C8.1, C9.1, J7.1, R14.2, R15.1, TP11.1 (1_1), U3.7 (VDD), U3.8 (VDD)
/AMP_SD: J1.9, R11.1, TP6.1 (1_1)
/BCLK: J1.4, R8.1, TP1.1 (1_1), U1.B2 (BCLK), U2.B2 (BCLK)
/BCLK_AMP: R8.2, U3.16 (BCLK)
/CLK_FL: J3.2, R2.2
/CLK_FR: J5.2, R3.2
/CLK_RL: J2.2, R4.2
/CLK_RR: J4.2, R5.2
/DIN_AMP: R10.2, U3.1 (DIN)
/GAIN_SLOT: R13.1, R14.1, U3.2 (GAIN_SLOT)
/GND: C1.2, C2.2, C3.2, C4.2, C5.2, C6.2, C7.2, C8.2, C9.2, C10.2, C11.2, J1.3, J1.5, J1.MP (MountPin), J2.3, J2.MP (MountPin), J3.3, J3.MP (MountPin), J4.3, J4.MP (MountPin), J5.3, J5.MP (MountPin), J6.MP (MountPin), J7.2, R6.2, R7.2, R12.2, R13.2, R16.2, TP12.1 (1_1), U1.C1 (GND), U2.C1 (GND), U3.3 (GND), U3.11 (GND), U3.15 (GND), U3.17 (PAD)
/LRCLK: J1.2, R9.1, TP2.1 (1_1), U1.C2 (LRCLK), U2.C2 (LRCLK)
/LRCLK_AMP: R9.2, U3.14 (LRCLK)
/MIC_FILT: FB1.2, R1.1
/OUTN: FB3.1, U3.10 (OUTN)
/OUTP: FB2.1, U3.9 (OUTP)
/PDM_CLK1: R2.1, R3.1, TP7.1 (1_1), U1.A2 (PDM_CLK)
/PDM_CLK2: R4.1, R5.1, TP8.1 (1_1), U2.A2 (PDM_CLK)
/PDM_DAT1: J3.4, J5.4, U1.A1 (PDM_DAT)
/PDM_DAT2: J2.4, J4.4, U2.A1 (PDM_DAT)
/SDI0: J1.8, R6.1, TP3.1 (1_1), U1.B1 (SDATA)
/SDI1: J1.7, R7.1, TP4.1 (1_1), U2.B1 (SDATA)
/SDO0: J1.6, R10.1, TP5.1 (1_1)
/SD_MODE: R11.2, R12.1, U3.4 (~SD_MODE)
/SPK_N: C11.1, FB3.2, J6.2
/SPK_P: C10.1, FB2.2, J6.1

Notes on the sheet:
Mic rail (D-067 F): passive, so never above the Pi's 3V3. 2.2 ohm damps the bead/C resonance near 34 kHz (Q 1.6 -> 0.12).
J2-J5: W27 mic leads, GH 1 3V3, 2 CLK, 3 GND, 4 DATA (PCB-06). REAR on J5-2/J5-4, FRONT on J5-3/J5-5 (D-067 D).
PDM clock: one series resistor per lead (source termination, edge <= 13 ns at the mic; tune on the bench).
SDATA tri-states outside its 20 bits: 100k pull-down per lane (ADAU7002 Fig. 11).
GAIN_SLOT: both open = 9 dB (default). R13 to GND: 0R 12 dB, 100k 15 dB. R14 to VDD: 0R 6 dB, 100k 3 dB. Fit one after the BO-007 bench listen (D-034 capped gain).
Amp: W12 5 V only (D-067 A). BCLK/LRCLK/DIN are 6 V-tolerant with VDD off; the 100 ohm resistors are edge damping.
SD_MODE is rated to VDD + 0.3 V: 2.2k limits it to ~1.2 mA with the branch off (datasheet remedy). No power-good path (D-067 C).
Unfitted 5V-present divider (5.0 V -> 3.0 V) on J5-1 pin 10, for a later CA-06 change (D-067 C).
H1-H3: M2 SMT spacers (8 mm) reflowed on the top face over plated Ø3 holes (D-067 I1), no net. Board-local (3.5, 30.0), (3.5, 8.0), (18.0, 19.0) (D-067 E).
